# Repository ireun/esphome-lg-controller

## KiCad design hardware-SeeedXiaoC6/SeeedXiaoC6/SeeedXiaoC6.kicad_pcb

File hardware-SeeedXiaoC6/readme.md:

# Seeed Xiao ESP32-C6 PCB Design

This version is for [Seeed Xiao ESP32-C6](https://wiki.seeedstudio.com/xiao_esp32c6_getting_started/), based on the `FeatherS3` revision.

PCB design by [@IreuN](https://github.com/ireun).

> **Note:** This design is untested and has never been produced. It is provided as-is, without any kind of warranty.

## Changes

* Added TestPoints (GND, 3V3, 12V)
* Added additional capacitor C3 on 3V3 output of TPS82130
* Added ability to mount XIAO directly or through header
* Reduced to 2 layers only
* Added GND stitching around the PCB
* Moved signal pin to the middle of JST connector
* Added a place for an IR diode, making it possible to use it when some functions are unavailable to set by CN-REMO but are available to an IR remote

## Images

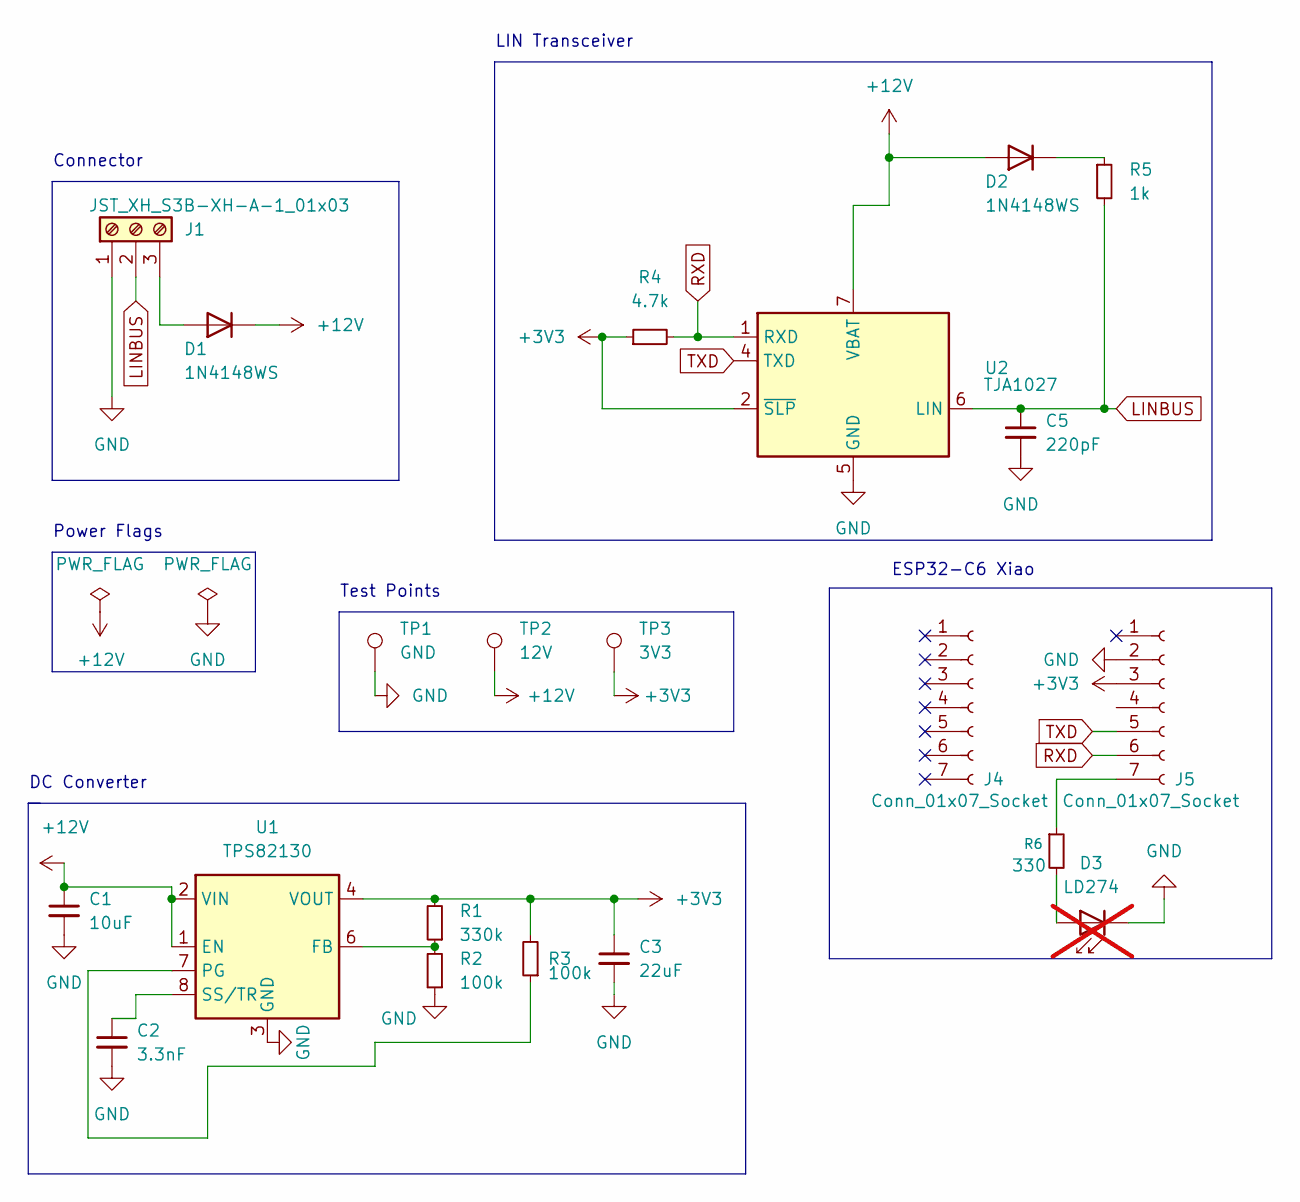
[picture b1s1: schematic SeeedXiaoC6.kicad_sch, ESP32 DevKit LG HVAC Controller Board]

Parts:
C1: 10uF; C_1210_3225Metric; LCSC C92834
C2: 3.3nF; C_0402_1005Metric; LCSC C26404
C3: 22uF; C_0805_2012Metric; LCSC C342717
C5: 220pF; C_0402_1005Metric; LCSC C343058
D1, D2: 1N4148WS; D_SOD-323; LCSC C727111
D3: LD274; LED_D5.0mm_IRGrey; not fitted
J1: JST_XH_S3B-XH-A-1_01x03; JST_XH_S3B-XH-A-1_1x03_P2.50mm_Horizontal; LCSC C157928
J4, J5: Conn_01x07_Socket; PinSocket_1x07_P2.54mm_Vertical
R1: 330k; R_0805_2012Metric; LCSC C17629
R2, R3: 100k; R_0805_2012Metric; LCSC C149504
R4: 4.7k; R_0805_2012Metric; LCSC C17673
R5: 1k; R_0805_2012Metric; LCSC C17513
R6: 330; R_0805_2012Metric
TP1: GND; TestPoint_Pad_D1.0mm
TP2: 12V; TestPoint_Pad_D1.0mm
TP3: 3V3; TestPoint_Pad_D1.0mm
U1: TPS82130; Texas_SIL0008D_MicroSiP-8-1EP_2.8x3mm_P0.65mm_EP1.1x1.9mm_T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; LCSC C473914
U2: TJA1027; SOIC-8_3.9x4.9mm_P1.27mm; LCSC C194371

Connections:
+3V3: C3.1, J5.3, R1.2, R3.2, R4.1, TP3.1, U1.4 (VOUT), U1.5 (VOUT), U2.2 (~SLP)
+12V: C1.1, D1.1 (K), D2.2 (A), TP2.1, U1.1 (EN), U1.2 (VIN), U2.7 (VBAT)
GND: C1.2, C2.2, C3.2, C5.2, D3.1 (K), J1.1, J5.2, R2.1, TP1.1, U1.3 (GND), U1.9 (GND), U2.5 (GND)
LINBUS: C5.1, J1.2, R5.2, U2.6 (LIN)
unnamed: D1.2 (A), J1.3
unnamed: D2.1 (K), R5.1
unnamed: D3.2 (A), R6.2
unnamed: J5.7, R6.1
unnamed: R1.1, R2.2, U1.6 (FB)
unnamed: R3.1, U1.7 (PG)
unnamed: C2.1, U1.8 (SS/TR)
RXD: J5.6, R4.2, U2.1 (RXD)
TXD: J5.5, U2.4 (TXD)

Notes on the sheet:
DC Converter
Connector
Test Points
LIN Transceiver
Power Flags
ESP32-C6 Xiao

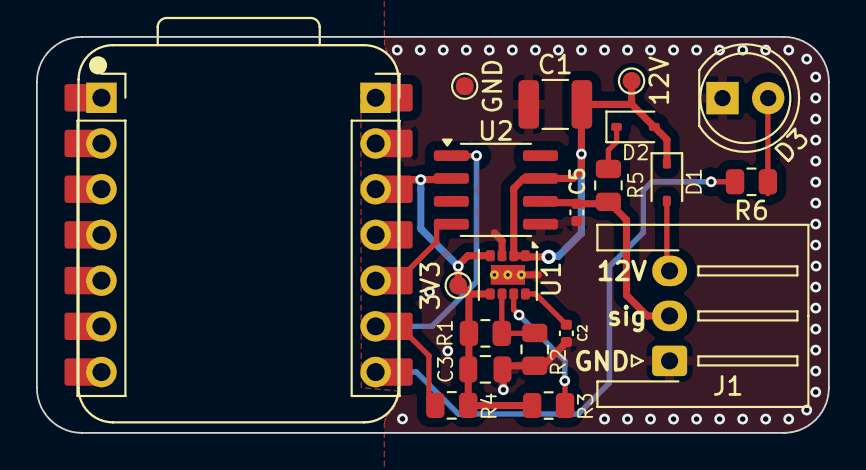
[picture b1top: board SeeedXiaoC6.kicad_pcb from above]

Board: 2 copper layers, 44.0 x 22.0 mm, 21 parts (0 on the bottom side), 13 nets.

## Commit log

2025-11-12 Add (work in progress) hardware version for Seeed Xiao ESP32-C6
2025-11-12 flatten dir
2025-11-12 Add images and readme.md
2025-11-12 Fix images
2025-11-12 Add url
2025-11-12 List changes
